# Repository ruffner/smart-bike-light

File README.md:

# smart-bike-light
Motion sensing bike light that automatically turns itself off.

Featuring an integrated SparkFun femtobuck constant current driver, seen in the upper left of the schematic, below.

A work in progress, waiting on the new analog accel board to be printed:

The corresponding schematic:

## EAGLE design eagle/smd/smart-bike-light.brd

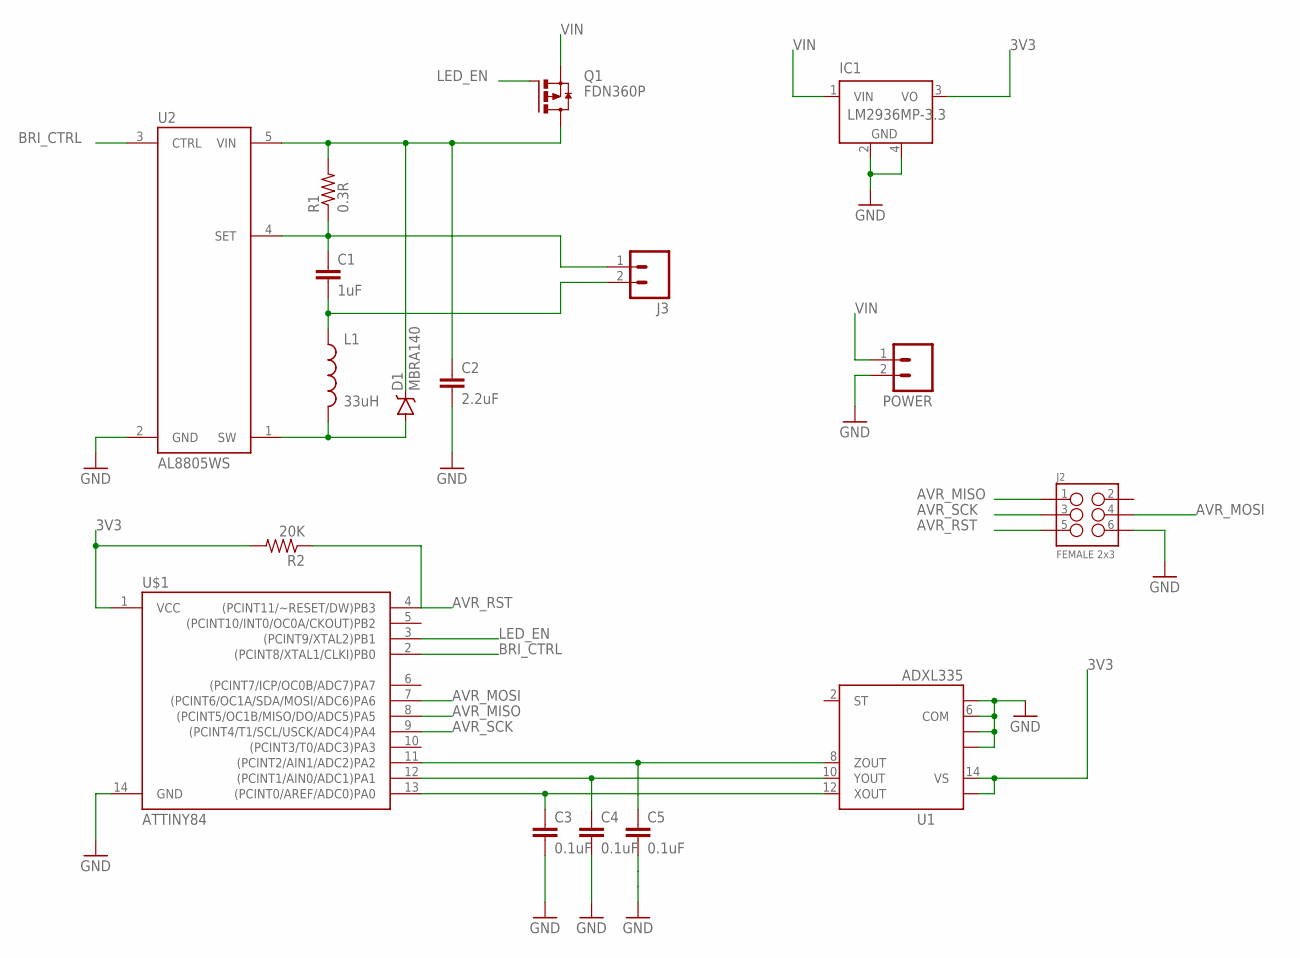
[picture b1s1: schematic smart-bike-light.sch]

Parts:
C1: 1uF; 0603-CAP
C2: 2.2uF; 0603-CAP
C3, C4, C5: 0.1uF; 0603-CAP
D1: MBRA140; SMA-DIODE
IC1: LM2936MP-3.3; SOT223
J2: FEMALE 2x3; 2X3
J3: M02PTH; 1X02
L1: 33uH; SRN6045
POWER: M02PTH; 1X02
Q1: FDN360P; SUPER-SOT3
R1: 0.3R; 0603-RES
R2: 20K; 0603-RES
U1: ADXL335; LFCSP-16
U2: AL8805WS; SOT23-5
U$1: ATTINY84; SO14

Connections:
3V3: IC1.3 (VO), R2.2, U1.14 (VS), U1.15 (VS), U$1.1 (VCC)
AVR_MISO: J2.1, U$1.8 ((PCINT5/OC1B/MISO/DO/ADC5)PA5)
AVR_MOSI: J2.4, U$1.7 ((PCINT6/OC1A/SDA/MOSI/ADC6)PA6)
AVR_RST: J2.5, R2.1, U$1.4 ((PCINT11/~RESET/DW)PB3)
AVR_SCK: J2.3, U$1.9 ((PCINT4/T1/SCL/USCK/ADC4)PA4)
BRI_CTRL: U2.3 (CTRL), U$1.2 ((PCINT8/XTAL1/CLKI)PB0)
GND: C2.2, C3.2, C4.2, C5.2, IC1.2 (GND), IC1.4 (GND), J2.6, POWER.2, U1.3 (COM), U1.5 (COM), U1.6 (COM), U1.7 (COM), U2.2 (GND), U$1.14 (GND)
LED_EN: Q1.1 (G), U$1.3 ((PCINT9/XTAL2)PB1)
unnamed: C1.1, J3.1, R1.1, U2.4 (SET)
unnamed: C2.1, D1.C, Q1.3 (D), R1.2, U2.5 (VIN)
unnamed: D1.A, L1.2, U2.1 (SW)
unnamed: C1.2, J3.2, L1.1
unnamed: C3.1, U1.12 (XOUT), U$1.13 ((PCINT0/AREF/ADC0)PA0)
unnamed: C4.1, U1.10 (YOUT), U$1.12 ((PCINT1/AIN0/ADC1)PA1)
unnamed: C5.1, U1.8 (ZOUT), U$1.11 ((PCINT2/AIN1/ADC2)PA2)
VIN: IC1.1 (VIN), POWER.1, Q1.2 (S)

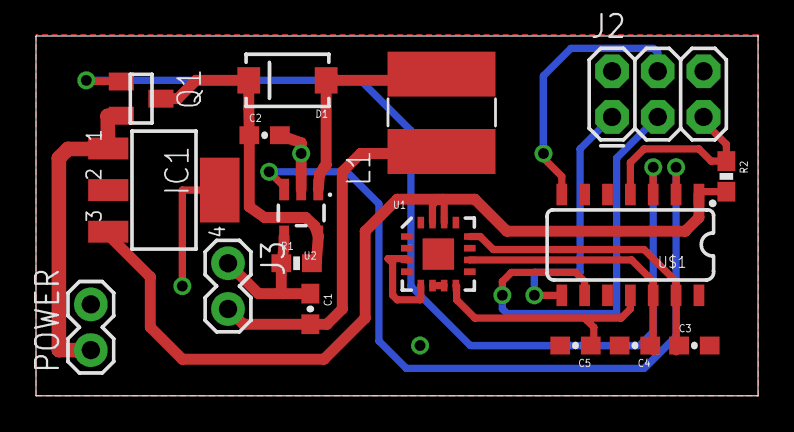
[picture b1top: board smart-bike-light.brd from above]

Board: 2 copper layers, 40.1 x 20.0 mm, 17 parts (0 on the bottom side), 16 nets.

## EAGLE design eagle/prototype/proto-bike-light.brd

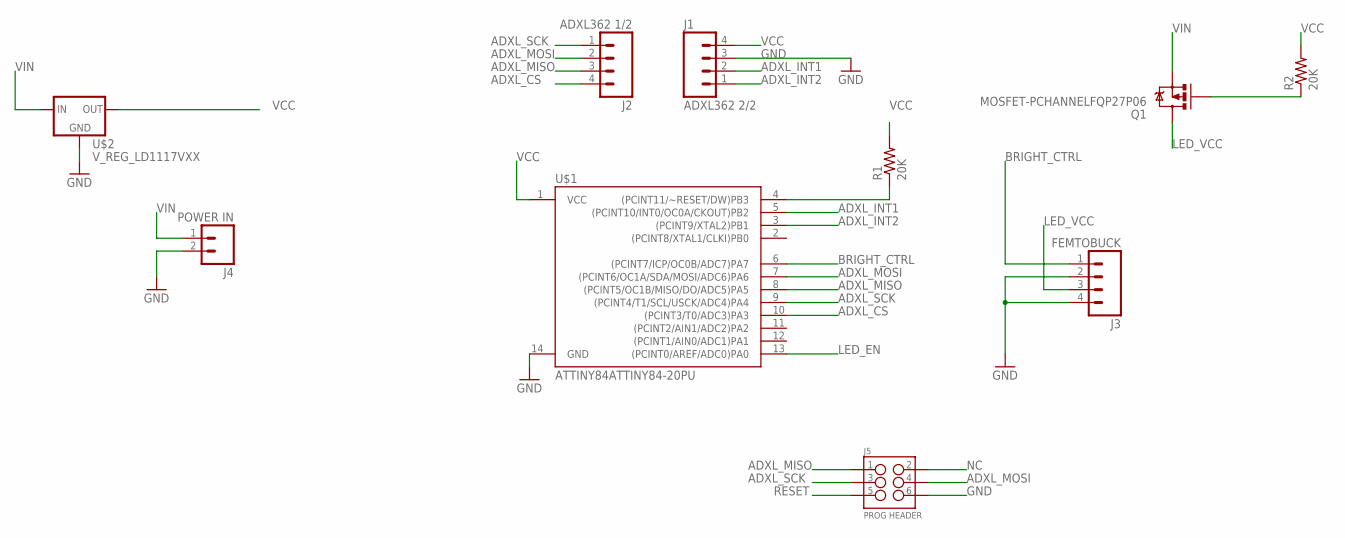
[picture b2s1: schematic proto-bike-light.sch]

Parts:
J1: ADXL362 2/2; 1X04
J2: ADXL362 1/2; 1X04
J3: FEMTOBUCK; 1X04
J4: POWER IN; 1X02
J5: PROG HEADER; 2X3
Q1: MOSFET-PCHANNELFQP27P06; TO220V
R1, R2: 20K; AXIAL-0.4
U$1: ATTINY84ATTINY84-20PU; DIL14
U$2: V_REG_LD1117VXX; 78XXL

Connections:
ADXL_CS: J2.4, U$1.10 ((PCINT3/T0/ADC3)PA3)
ADXL_INT1: J1.2, U$1.5 ((PCINT10/INT0/OC0A/CKOUT)PB2)
ADXL_INT2: J1.1, U$1.3 ((PCINT9/XTAL2)PB1)
ADXL_MISO: J2.3, J5.1, U$1.8 ((PCINT5/OC1B/MISO/DO/ADC5)PA5)
ADXL_MOSI: J2.2, J5.4, U$1.7 ((PCINT6/OC1A/SDA/MOSI/ADC6)PA6)
ADXL_SCK: J2.1, J5.3, U$1.9 ((PCINT4/T1/SCL/USCK/ADC4)PA4)
BRIGHT_CTRL: J3.1, U$1.6 ((PCINT7/ICP/OC0B/ADC7)PA7)
GND: J1.3, J3.2, J3.4, J4.2, J5.6, U$1.14 (GND), U$2.IN (GND)
LED_EN: Q1.1 (G), R2.P$1 (1), U$1.13 ((PCINT0/AREF/ADC0)PA0)
LED_VCC: J3.3, Q1.2 (D)
NC: J5.2
RESET: J5.5, R1.P$1 (1), U$1.4 ((PCINT11/~RESET/DW)PB3)
VCC: J1.4, R1.P$2 (2), R2.P$2 (2), U$1.1 (VCC), U$2.GND (OUT)
VIN: J4.1, Q1.3 (S), U$2.OUT (IN)

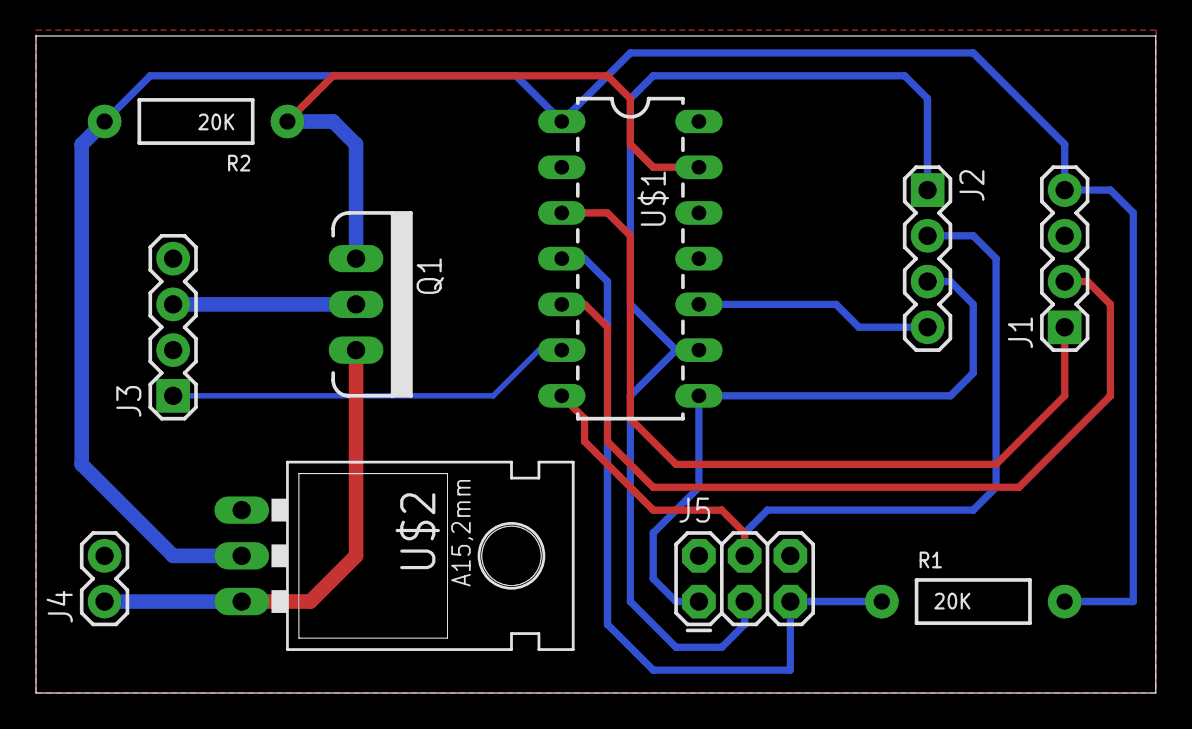
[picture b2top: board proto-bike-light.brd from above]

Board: 2 copper layers, 62.2 x 36.5 mm, 10 parts (0 on the bottom side), 13 nets.

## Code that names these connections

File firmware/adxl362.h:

/*
AVR library for the Analog Devices ADXL362 
ultra low power 3 axis accelerometer
Written for attiny device's USI

Matt Ruffner 2014
 */

#ifndef ADXL362_H
#define ADXL362_H

#include <avr/io.h>
#include <inttypes.h>


//////////////////////
// funtion definitions
//////////////////////

// preliminary
void adxl362_begin();

// measurement
void read_all_axes(int16_t * data);
void read_all_axes_short(int8_t * data);
int16_t read_axis(int axis);
int8_t read_axis_short(int axis);
int16_t read_temp();

// configuration
void config_linkloop(uint8_t mode);
void config_measure_mode(uint8_t mode); // requried call after reset
void config_range(uint8_t range);
void config_odr(uint8_t odr);
void config_int1(uint8_t int_source, uint8_t direction, uint8_t pullup);
void config_int2(uint8_t int_source, uint8_t direction, uint8_t pullup);
void config_act_int(uint16_t thresh, uint8_t time);
void config_inact_int(uint16_t thresh, uint16_t time);

// basic io
uint8_t read_reg(uint8_t reg);
uint16_t read_reg16(uint8_t reg);
void read_fifo(uint8_t * data, uint16_t len);
void write_reg(uint8_t reg, uint8_t value);
void write_reg16(uint8_t reg, uint16_t value);
uint8_t usi_transfer(uint8_t data);


// USI pin definitions
#define ADXL_DDR     DDRA
#define ADXL_PORT    PORTA
#define ADXL_MOSI    PA5
#define ADXL_MISO    PA6
#define ADXL_SCK     PA4
#define ADXL_CS      PA3
#define ADXL_CS_HIGH ADXL_PORT |= (1 << ADXL_CS)
#define ADXL_CS_LOW  ADXL_PORT &= ~(1 << ADXL_CS)

// interrupt pin definitions if ya want em
#define ADXL362_INT1_DDR  DDRB
#define ADXL362_INT1_PORT PORTB
#define ADXL362_INT1_PIN  PINB
#define ADXL362_INT2_DDR  DDRB
#define ADXL362_INT2_PORT PORTB
#define ADXL362_INT2_PIN  PINB
#define ADXL362_INT1      PB2
#define ADXL362_INT2      PB1

// axis definitions for read functions
#define X 0
#define Y 1
#define Z 2

///////////////////////////////
// ADXL362 register definitions
///////////////////////////////

// spi commands
#define ADXL362_WRITE_REGISTER 0x0A
#define ADXL362_READ_REGISTER  0x0B
#define ADXL362_READ_FIFO      0x0D

// identification registers, will always read the same
#define DEVID_AD    0x00
#define DEVID_MST   0x01
#define PARTID      0x02
#define REVID       0x03

// 8 bit resolution, power saving, registers
#define XDATA       0x08
#define YDATA       0x09
#define ZDATA       0x0A

// 12 bit, full resolution, sign extended data registers
// therefor the 4 MSBs of the _H register are all the same 
// and contain the sign of the reading
#define XDATA_L  0x0E
#define XDATA_H  0x0F
#define YDATA_L  0x10
#define YDATA_H  0x11
#define ZDATA_L  0x12
#define ZDATA_H  0x13

// 12 bit sign extended temperature registers
#define TEMP_L 0x14
#define TEMP_H 0x15

// status register
#define ADXL_STATUS          0x0B
#define ERR_USER_REGS   7
#define AWAKE           6
#define INACT           5
#define ACT             4
#define FIFO_OVERRUN    3
#define FIFO_WATERMARK  2
#define FIFO_READY      1
#define DATA_READY      0

// soft reset register, write 0x52, 'R' in ascii, to reset the devce
#define SOFT_RESET 0x1F

// FIFO entries register, the 10 bit number representing the
//  how many valid data samples are int the FIFO buffer
#define FIFO_ENTRIES_L  0x0C
#define FIFO_ENTRIES_H  0x0D

// activity threshold registers
// 11 bit, unsigned value to be compared with the 12 bit
// signed acceleration value
#define THRESH_ACT_L 0x20
#define THRESH_ACT_H 0x21

// activity time register, when used, the duration of motion 
// must be sustained for this amount of time to trigger activity
// detection caclulated by actual time = TIME_ACT/ODR
#define TIME_ACT 0x22

// inactivity threshold registers
// 11 bit unsigned value to be compared to the magnitude of the 
// acceleration value
#define THRESH_INACT_L 0x23
#define THRESH_INACT_H 0x24

// inactivity time registers, a 16 bit value
// actual time = TIME_INACT/ODR, a maximum of almost 90 minutes
#define TIME_INACT_L 0x25
#define TIME_INACT_H 0x26

// (in)activity control register
#define ACT_INACT_CTL 0x27
#define LINKLOOP   4 // 2 bit value
#define INACT_REF  3
#define INACT_EN   2
#define ACT_REF    1
#define ACT_EN     0

#define LINKLOOP_DEFAULT 0
#define LINKLOOP_LINKED  1
#define LINKLOOP_LOOP    2

// FIFO control register
#define FIFO_CONTROL 0x28
#define AH        3
#define FIFO_TEMP 2
#define FIFO_MODE 0 // 2 bit value

// FIFO samples register
// MSbit is AH in FIFO_CONTROL
#define FIFO_SAMPLES 0x29 // defaults to 0x80

// INT1/INT2 function map registers
#define INTMAP1 0x2A
#define INTMAP2 0x2B
#define INT_LOW        7
#define AWAKE          6 
#define INACT          5 
#define ACT            4
#define FIFO_OVERRUN   3
#define FIFO_WATERMARK 2
#define FIFO_READY     1
#define DATA_READY     0

// filter control register
#define FILTER_CTL 0x2C
#define RANGE      6    // 2 bit value
#define HALF_BW    4
#define EXT_SAMPLE 3
#define ODR        0    // 3 bit value

#define RANGE_2G 0
#define RANGE_4G 1
#define RANGE_8G 2

#define ODR_12_5_HZ 0
#define ODR_25_HZ   1
#define ODR_50_HZ   2
#define ODR_100_HZ  3 // reset default
#define ODR_200_HZ  4
#define ODR_400_HZ  5

// power control register
#define POWER_CTL 0x2D
#define EXT_CLK   6
#define LOW_NOISE 4     // 2 bit value
#define WAKEUP    3
#define AUTOSLEEP 2
#define MEASURE   0     // 2 bit value

#define MODE_STANDBY 0 // reset default
#define MODE_MEASURE 2

// self test register
#define SELF_TEST 0x2E
#define ST 0

#endif

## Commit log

2016-08-02 added planned schematic
2016-08-03 added work on schematic and board design.
2016-08-04 added prototype board with through hole components, programming header and no led driver
2016-08-04 added adxl362 library and makefile
2016-08-06 updated adxl362 pin pin definitions, testing accel communication.
2016-08-06 updated accel code
2016-08-08 added prototype schematic for coding reference.
2016-08-10 switched to analog accel
2016-08-10 updated jumper silkscreens, README

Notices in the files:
parts and their libraries:
SparkFun-Connectors: Licensing: Creative Commons ShareAlike 4.0 International - https://creativecommons.org/licenses/by-sa/4.0
